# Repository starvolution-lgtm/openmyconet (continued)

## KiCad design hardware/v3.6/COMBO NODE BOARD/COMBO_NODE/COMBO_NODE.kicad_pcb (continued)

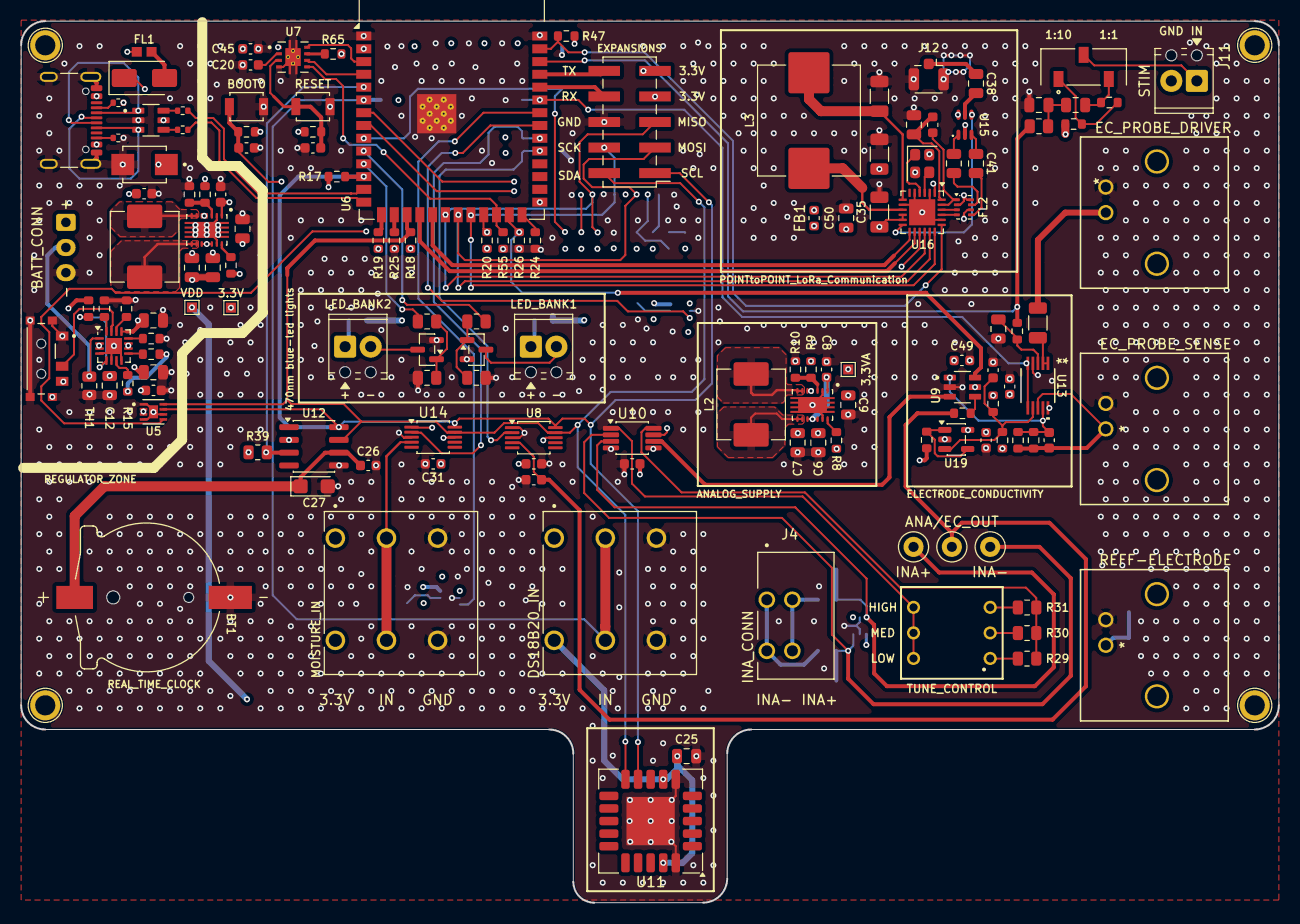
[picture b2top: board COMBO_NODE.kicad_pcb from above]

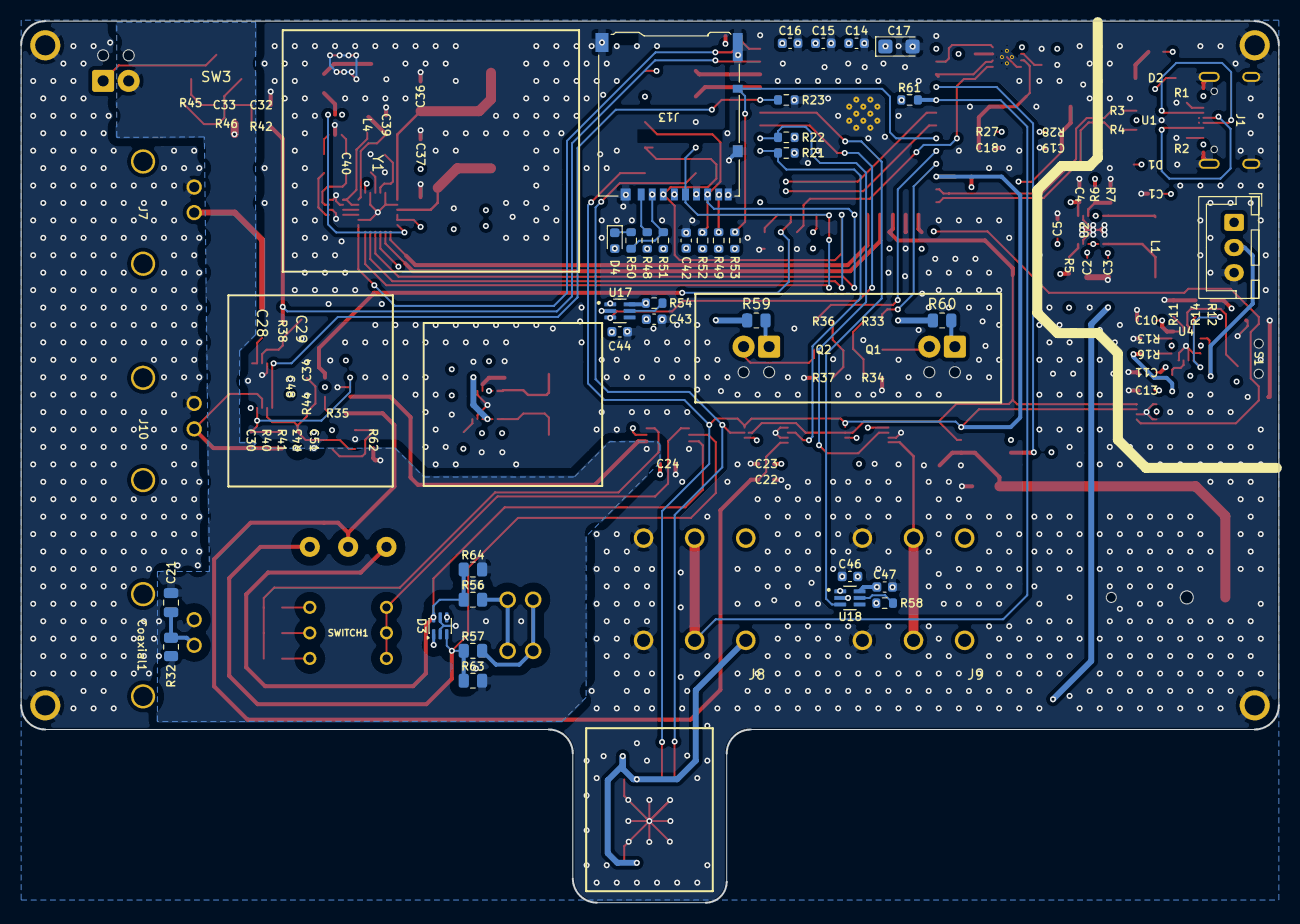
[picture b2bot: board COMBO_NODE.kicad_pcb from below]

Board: 4 copper layers, 125.0 x 87.6 mm, 180 parts (35 on the bottom side), 123 nets.

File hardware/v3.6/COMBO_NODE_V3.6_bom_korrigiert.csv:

Designator,Footprint,Quantity,Value,LCSC Part #
BT1,BAT_CH291-1220LF,1,CH291-1220LF,
"C1, C13, C14, C15, C16, C18, C19, C20, C23, C24, C26, C31, C34, C4, C42, C45, C48, C49, C8, C51",603,20,100nF,
C10,805,1,1uF,
"C11, C12",805,2,4.7uF,
"C17, C27",CP_EIA-3216-18_Kemet-A,2,10uF,C7171
"C2, C3, C33, C6, C7",805,5,10uF,
"C21, C25, C39, C50",805,4,100nF,
C22,603,1,1nF,
C28,1206,1,100uF,
"C29, C32",805,2,10nF,
C30,603,1,10pF,
C35,1206,1,47uF,
C36,1206,1,470nF,
C37,1206,1,10uF,
"C38, C40, C41",805,3,47pF,
"C43, C47",603,2,47uF,
"C44, C46",603,2,10uF,
"C5, C9",805,2,47uF,
COAXIAL1,CONN_73137-5003_MOL,1,REFF-ELECTRODE,
D1,SMBJ5.0A,1,SMBJ5.0A,C83333
D2,D_SMA,1,SS34,C8678
D3,SOT-363_SC-70-6,1,BAV199DW,C3034809
D4,603,1,LED,
FB1,603,1,FerriteBead,
FL1,BEADC1608X95N,1,BLM18PG121SN1D,C14709
FL2,Balun_Johanson_0900FM15K0039,1,0900FM15K0039,C7434807
J1,USB_C_Receptacle_GCT_USB4105-xx-A_16P_TopMnt_Horizontal,1,USB_C_Receptacle_USB2.0_16P,C2765186
J10,CONN_73137-5003_MOL,1,EC_PROBE_SENSE,
J11,"TerminalBlock_Phoenix_MPT-0,5-2-2.54_1x02_P2.54mm_Horizontal",1,STIM,C3029316
J12,U.FL_Hirose_U.FL-R-SMT-1_Vertical,1,Conn_Coaxial_Small,C88374
J13,microSD_HC_Hirose_DM3AT-SF-PEJM5,1,Micro_SD_Card_Det_Hirose_DM3AT,C114218
J2,JST_XH_B3B-XH-A_1x03_P2.50mm_Vertical,1,BATT_CONN,C144394
J3,PinHeader_2x05_P2.54mm_Vertical_SMD,1,EXPANSIONS,C55213916
J4,PHOENIX_1789618,1,INA_CONN,C17577890
J5,"TerminalBlock_Phoenix_MPT-0,5-2-2.54_1x02_P2.54mm_Horizontal",1,LED_BANK2,C3029316
J6,"TerminalBlock_Phoenix_MPT-0,5-2-2.54_1x02_P2.54mm_Horizontal",1,LED_BANK1,C3029316
J7,CONN_73137-5003_MOL,1,EC_PROBE_DRIVER,
J8,PHOENIX_1790296,1,DS18B20_IN,C7472194
J9,PHOENIX_1790296,1,MOISTURE_IN,C7472194
"L1, L2",L_APV_APH0630,2,1.5uH,C5349697
L3,L_APV_APH1040,1,15uH,C5349716
L4,603,1,27nH,
"Q1, Q2",SOT-23,2,BSS138,
"R1, R2",402,2,5.1K,
"R10, R7",603,2,180K,
R11,603,1,46.4K,
"R12, R15, R16, R19, R20, R21, R22, R23, R24, R25, R26, R27, R28, R47, R48, R49, R51, R52, R53",603,19,10K,
R13,603,1,1.18K,
R14,603,1,1.13K,
"R17, R18, R61",603,3,4.7K,
"R29, R32, R33, R36",805,4,100,
"R3, R4",402,2,27,
"R30, R42, R56, R57",805,4,1K,
"R31, R34, R37, R39",805,4,10K,
R35,603,1,100,
"R38, R46, R50, R54, R58",603,5,1K,
"R40, R41",603,2,3.3K,
"R43, R44, R5, R55, R65, R8",603,6,100K,
R45,603,1,9K,
"R59, R60",805,2,68,
"R6, R9",603,2,1M,
R62,603,1,22,
"R63, R64",805,2,10M,
S1,SW_MSK12C02,1,SWITCH,C431540
SW1,SW_SPST_B3U-1000P,1,RESET,C231329
SW2,SW_SPST_B3U-1000P,1,BOOT0,C231329
SW3,SW_JS102011JCQN,1,ATTENTUATOR_SELECT,
SWITCH1,418117270903,1,TUNE_CONTROL,C5299504
TP1,TestPoint_Pad_1.0x1.0mm,1,3.3V,
TP10,TestPoint_Loop_D1.80mm_Drill1.0mm_Beaded,1,INA-,
TP2,TestPoint_Pad_1.0x1.0mm,1,3.3VA,
"TP3, TP4, TP5, TP6",TestPoint_Plated_Hole_D2.0mm,4,GND,
TP7,TestPoint_Pad_1.0x1.0mm,1,VDD,
TP8,TestPoint_Loop_D1.80mm_Drill1.0mm_Beaded,1,ANA/EC_OUT,
TP9,TestPoint_Loop_D1.80mm_Drill1.0mm_Beaded,1,INA+,
U1,USBLC6-2SC6,1,USBLC6-2SC6,C7519
U10,VSSOP-8_3x3mm_P0.65mm,1,INA333AIDGK,C19450
U11,Sensirion_SCD4x-1EP_10.1x10.1mm_P1.25mm_EP4.8x4.8mm,1,SCD41-D-R2,C2867540
U12,SOIC-8_3.9x4.9mm_P1.27mm,1,DS3231MZ,C107410
U13,DGS10_TEX,1,OPA2320SAIDGSR,C2058677
"U14, U8",TSSOP-10_3x3mm_P0.5mm,2,ADS1115IDGSR,C37593
U15,SOT65P215X110-6N,1,PE4259,C470892
U16,QFN-24-1EP_4x4mm_P0.5mm_EP2.6x2.6mm,1,SX1262IMLTRT,C191341
"U17, U18",SOT65P210X110-6N,2,TPS22919DCKR,C2149796
"U2, U3",IC_TPS63020DSJT,2,TPS63020DSJR,C15483
U4,VQFN-16-1EP_3x3mm_P0.5mm_EP1.6x1.6mm,1,BQ24075RGT,C15464
U5,SON50P200X200X80-9N,1,MAX17048G+T10,C2682616
U6,ESP32-S3-WROOM-1,1,ESP32-S3-WROOM-1-N16R8,C2913202
U7,IC_DRV8601DRBT,1,TPS3851H33EDRBR,C717624
U9,SOT95P280X145-6N,1,TS5A3159DBVR,C42411032
U19,SOT-23-5,1,OPA333AIDBVR,C30878
Y1,Crystal_SMD_2520-4Pin_2.5x2.0mm,1,32MHz,C2842280
